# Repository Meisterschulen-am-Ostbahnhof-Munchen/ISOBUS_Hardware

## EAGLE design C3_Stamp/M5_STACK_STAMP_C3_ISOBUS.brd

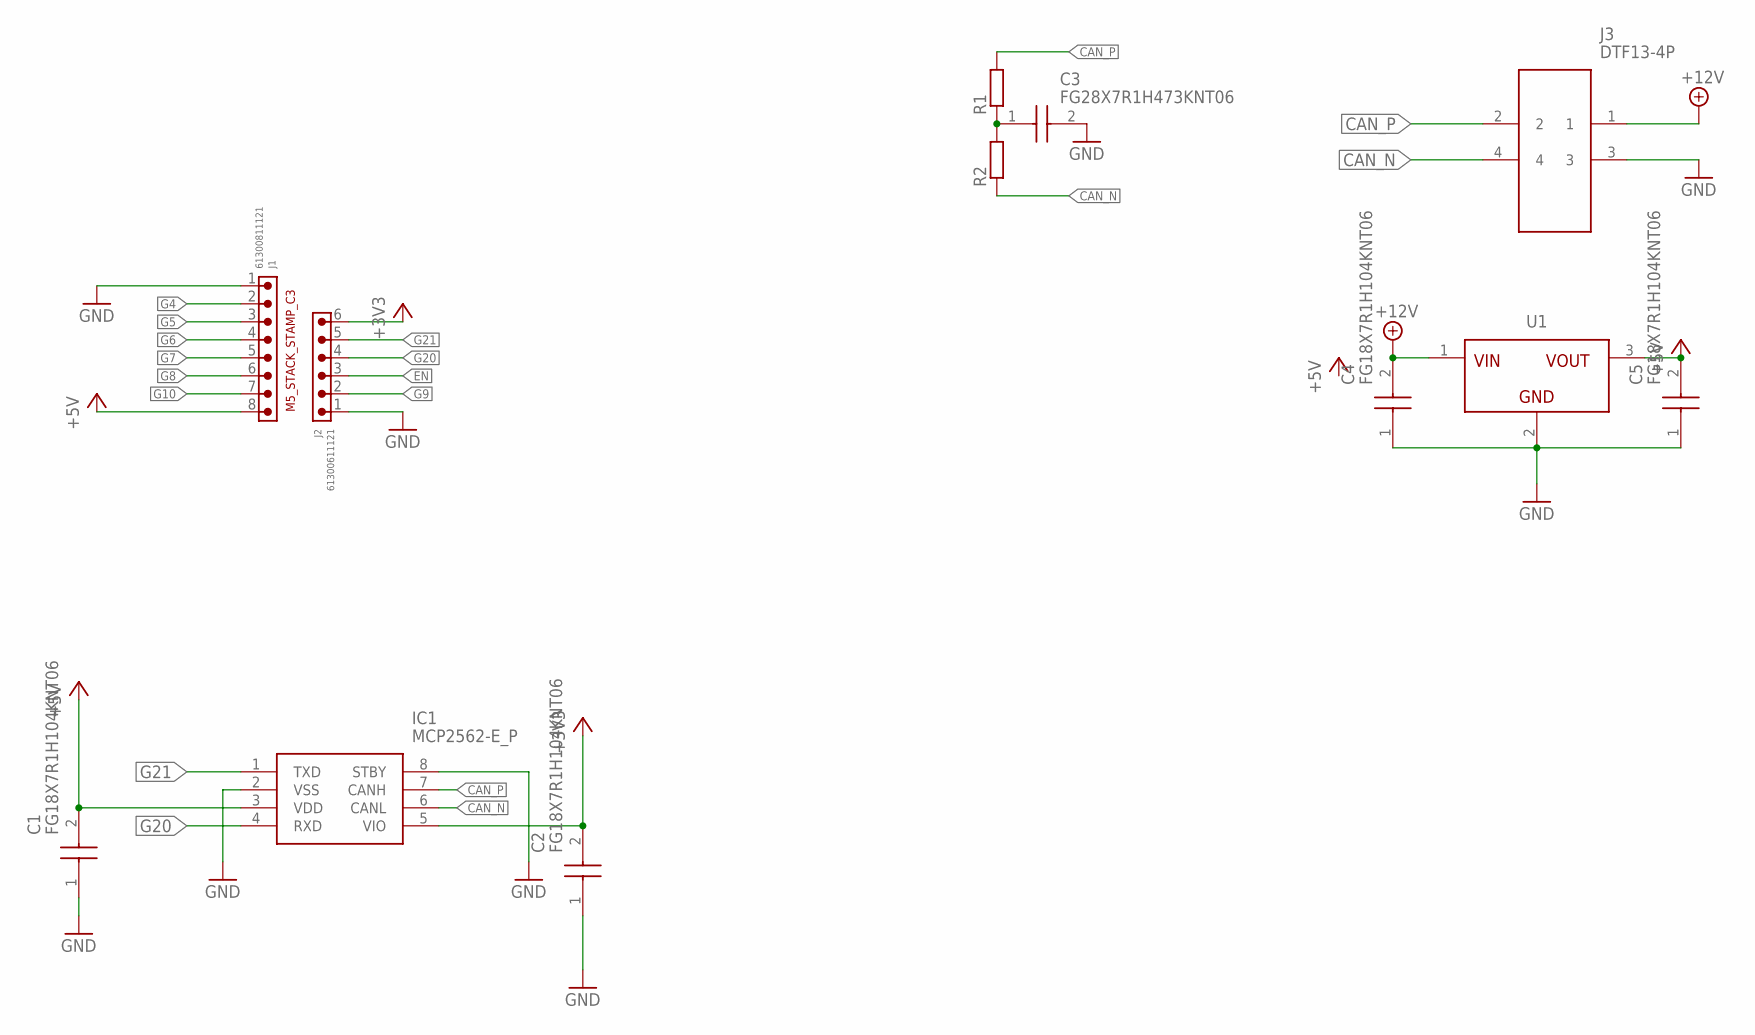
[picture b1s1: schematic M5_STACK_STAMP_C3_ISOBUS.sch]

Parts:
C1, C2, C4, C5: FG18X7R1H104KNT06; FG18C0G1H101JNT06
C3: FG28X7R1H473KNT06; FG28
IC1: MCP2562-E_P; DIP781W56P254L950H533Q8N
J1: 61300811121
J2: 61300611121
J3: DTF13-4P; DTF134P
R1, R2: R-EU_0204/7; 0204/7
U1: MAGI³C-FDSM_SIP-3_173010542_173XXXX42; MAGI³C-FDSM_173XXXX42
U$1: M5_STACK_STAMP_C3

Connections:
+3V3: C2.2, IC1.5 (VIO), J2.6
+5V: C1.2, C5.2, IC1.3 (VDD), J1.8, U1.3 (VOUT)
+12V: C4.2, J3.1, U1.1 (VIN)
CAN_N: IC1.6 (CANL), J3.4, R2.1
CAN_P: IC1.7 (CANH), J3.2, R1.2
EN: J2.3
G4: J1.2
G5: J1.3
G6: J1.4
G7: J1.5
G8: J1.6
G9: J2.2
G10: J1.7
G20: IC1.4 (RXD), J2.4
G21: IC1.1 (TXD), J2.5
GND: C1.1, C2.1, C3.2, C4.1, C5.1, IC1.2 (VSS), IC1.8 (STBY), J1.1, J2.1, J3.3, U1.2 (GND)
unnamed: C3.1, R1.1, R2.2

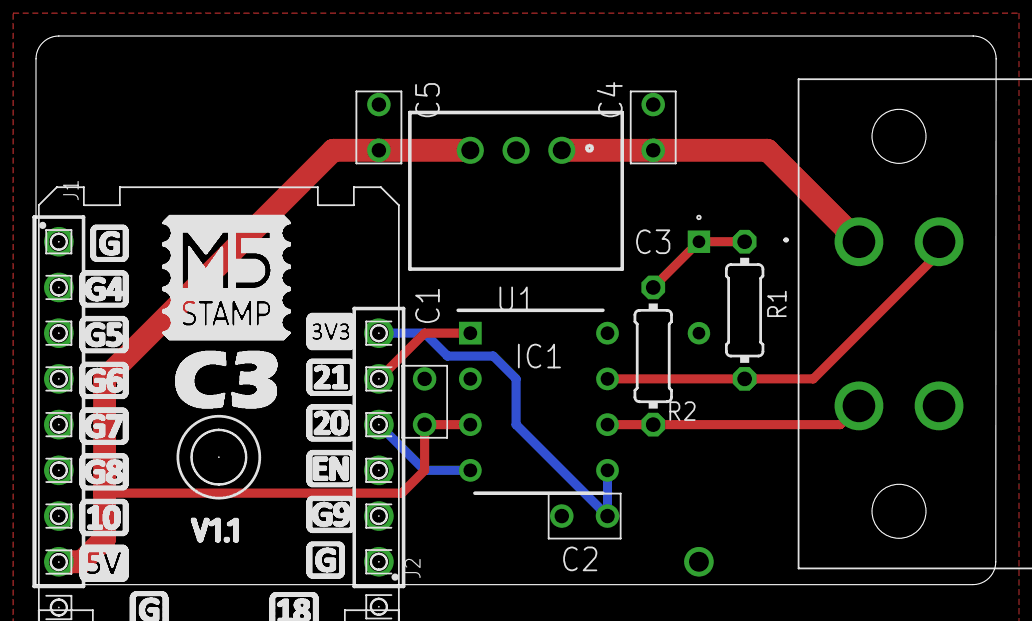
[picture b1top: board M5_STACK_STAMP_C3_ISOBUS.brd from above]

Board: 2 copper layers, 53.3 x 30.5 mm, 13 parts (0 on the bottom side), 9 nets.

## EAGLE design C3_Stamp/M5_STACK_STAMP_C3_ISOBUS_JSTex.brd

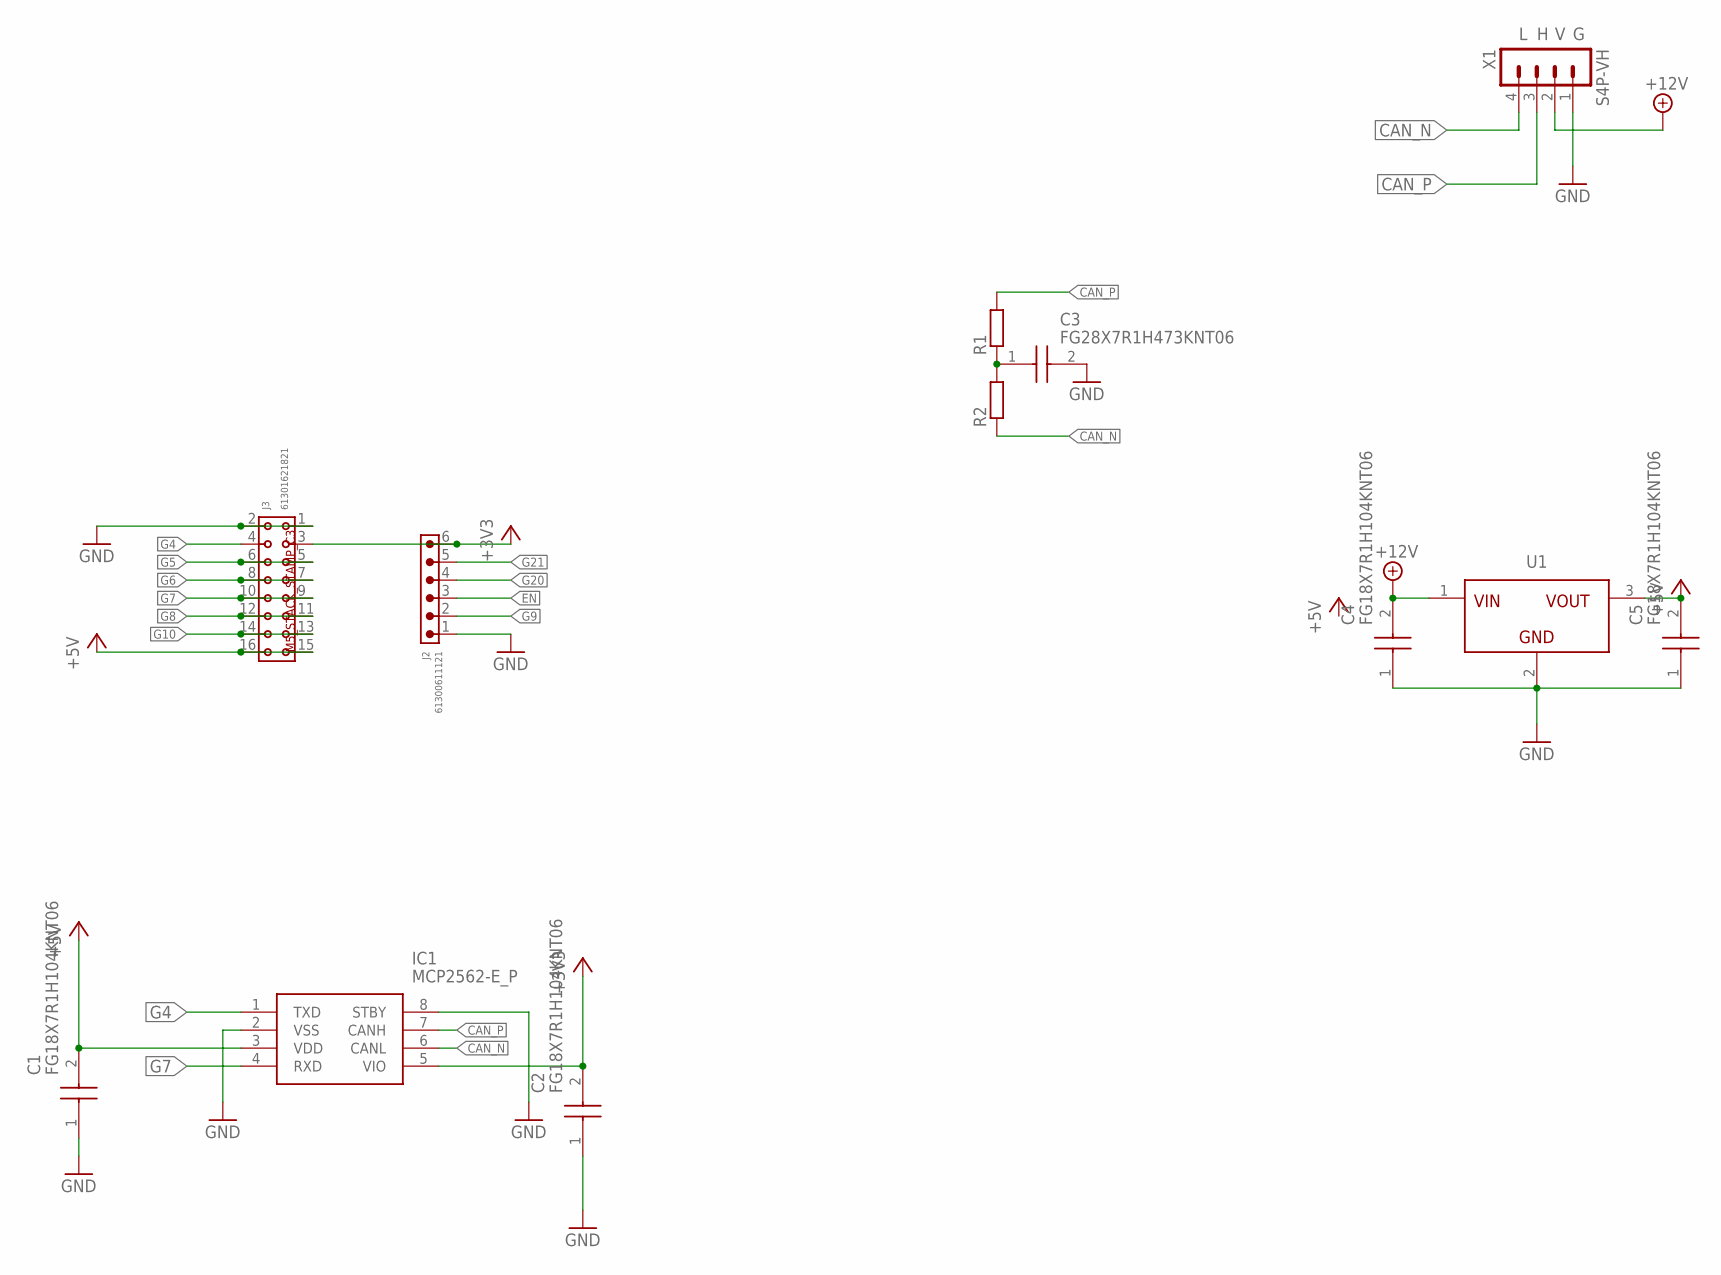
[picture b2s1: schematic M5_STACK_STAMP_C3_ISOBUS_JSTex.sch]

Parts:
C1, C2, C4, C5: FG18X7R1H104KNT06; FG18C0G1H101JNT06
C3: FG28X7R1H473KNT06; FG28
IC1: MCP2562-E_P; DIP781W56P254L950H533Q8N
J2: 61300611121
J3: 61301621821
R1, R2: R-EU_0204/7; 0204/7
U1: MAGI³C-FDSM_SIP-3_173010542_173XXXX42; MAGI³C-FDSM_173XXXX42
U$1: M5_STACK_STAMP_C3
X1: S4P-VH

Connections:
+3V3: C2.2, IC1.5 (VIO), J2.6, J3.3
+5V: C1.2, C5.2, IC1.3 (VDD), J3.15, J3.16, U1.3 (VOUT)
+12V: C4.2, U1.1 (VIN), X1.2
CAN_N: IC1.6 (CANL), R2.1, X1.4
CAN_P: IC1.7 (CANH), R1.2, X1.3
EN: J2.3
G4: IC1.1 (TXD), J3.4
G5: J3.5, J3.6
G6: J3.7, J3.8
G7: IC1.4 (RXD), J3.9, J3.10
G8: J3.11, J3.12
G9: J2.2
G10: J3.13, J3.14
G20: J2.4
G21: J2.5
GND: C1.1, C2.1, C3.2, C4.1, C5.1, IC1.2 (VSS), IC1.8 (STBY), J2.1, J3.1, J3.2, U1.2 (GND), X1.1
unnamed: C3.1, R1.1, R2.2

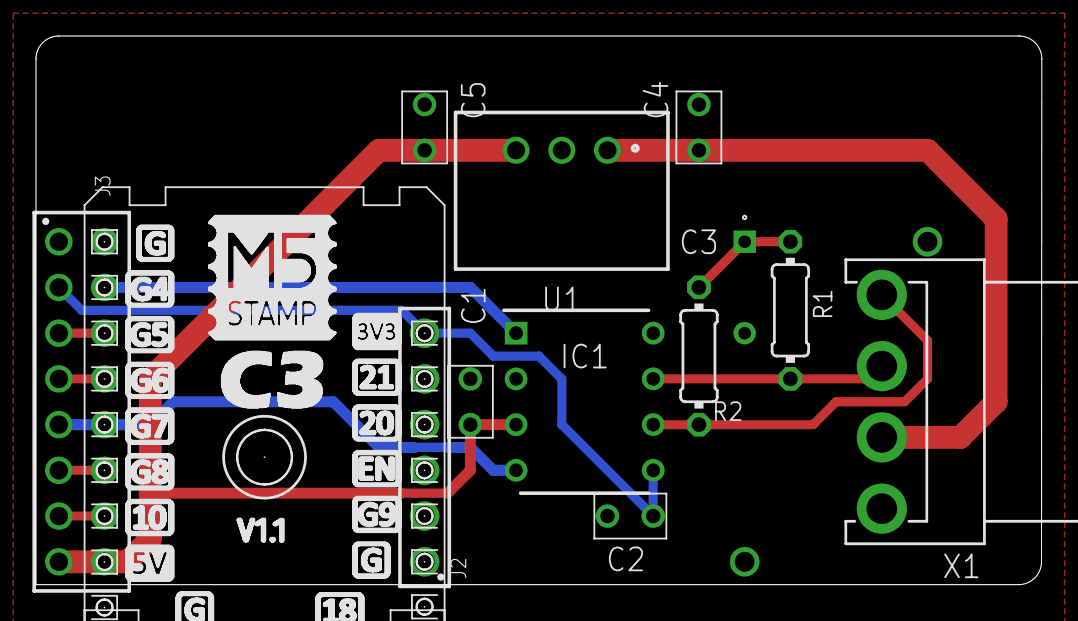
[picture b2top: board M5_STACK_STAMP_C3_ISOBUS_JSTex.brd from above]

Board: 2 copper layers, 55.9 x 30.5 mm, 13 parts (0 on the bottom side), 13 nets.

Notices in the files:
parts and their libraries:
Wurth_Connectors_WR-PHD: Copyright: Würth Elektronik
